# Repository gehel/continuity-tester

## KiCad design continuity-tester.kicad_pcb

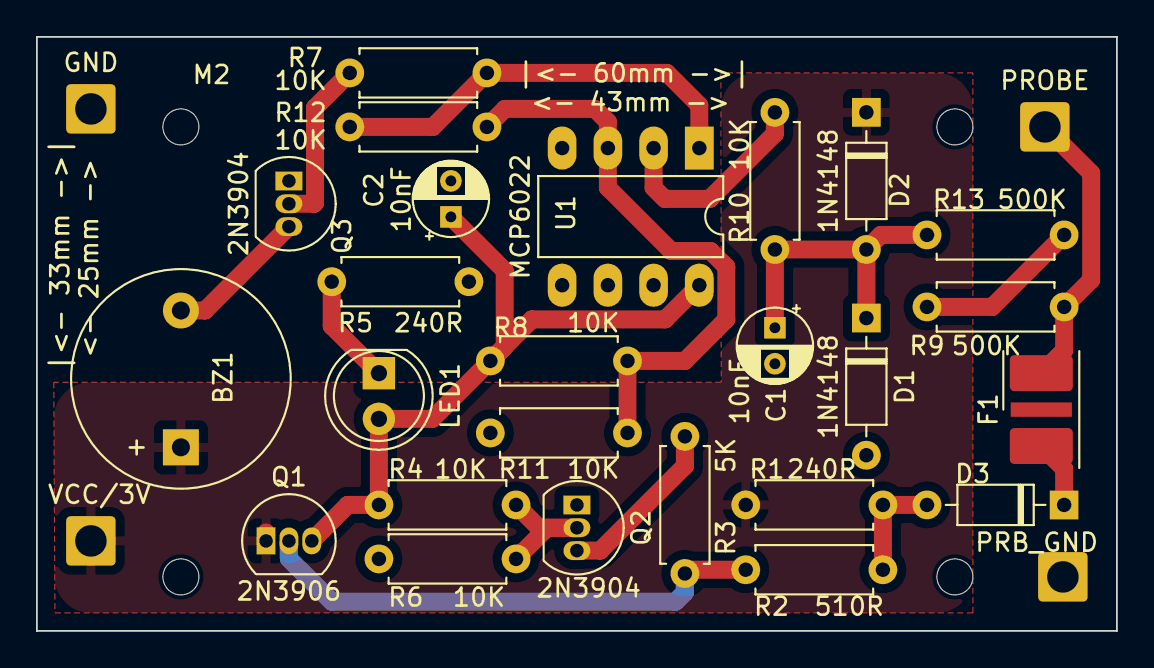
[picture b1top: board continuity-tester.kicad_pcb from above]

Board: 2 copper layers, 60.0 x 33.0 mm, 33 parts (0 on the bottom side), 17 nets.

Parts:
BZ1: Buzzer; Buzzer_12x9.5RM7.6
C1, C2: 10nF; CP_Radial_D4.0mm_P2.00mm
D1, D2: 1N4148; D_DO-35_SOD27_P7.62mm_Horizontal
D3: D; D_DO-35_SOD27_P7.62mm_Horizontal
F1: Polyfuse; Fuse_Bourns_TBU-CA
GND: Conn_01x01_Pin; SolderWire-1sqmm_1x01_D1.4mm_OD2.7mm
H1, H2, H3, H4: MountingHole_Pad; MountingHole_2mm
LED1: LED; LED_D5.0mm
PRB_GND: Conn_01x01_Pin; SolderWire-1sqmm_1x01_D1.4mm_OD2.7mm
PROBE: Conn_01x01_Pin; SolderWire-1sqmm_1x01_D1.4mm_OD2.7mm
Q1: 2N3906; TO-92_Inline
Q2, Q3: 2N3904; TO-92_Inline
R1, R5: 240R; R_Axial_DIN0207_L6.3mm_D2.5mm_P7.62mm_Horizontal
R2: 510R; R_Axial_DIN0207_L6.3mm_D2.5mm_P7.62mm_Horizontal
R3: 5K; R_Axial_DIN0207_L6.3mm_D2.5mm_P7.62mm_Horizontal
R4, R6, R7, R8, R10, R11, R12: 10K; R_Axial_DIN0207_L6.3mm_D2.5mm_P7.62mm_Horizontal
R9, R13: 500K; R_Axial_DIN0207_L6.3mm_D2.5mm_P7.62mm_Horizontal
U1: MCP6022; DIP-8_W7.62mm_LongPads
VCC/3V: Conn_01x01_Pin; SolderWire-1sqmm_1x01_D1.4mm_OD2.7mm

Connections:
GND: C1.2, C2.2, D1.2 (A), GND.1, PRB_GND.1, Q2.1 (E), Q3.1 (E), R5.1, R6.1, R11.1, U1.4 (V-)
unnamed: BZ1.2 (+), Q3.3 (C)
unnamed: C1.1, D1.1 (K), D2.2 (A), R10.1, R13.2
unnamed: D3.2 (A), R1.1, R2.1
unnamed: D3.1 (K), F1.1
unnamed: F1.2, PROBE.1, R9.1
unnamed: LED1.1 (K), R5.2
unnamed: Q1.2 (B), R2.2, R3.2
unnamed: Q2.2 (B), R4.1, R6.2
unnamed: Q2.3 (C), R3.1
unnamed: Q3.2 (B), R7.2
unnamed: R7.1, R12.2, U1.1
unnamed: R9.2, R13.1
unnamed: R8.1, R11.2, R12.1, U1.3 (+)
unnamed: R10.2, U1.2 (-)
POWER_SWITCHED: C2.1, LED1.2 (A), Q1.3 (C), R4.2, R8.2, U1.8 (V+)
VCC: BZ1.1 (-), D2.1 (K), Q1.1 (E), R1.2, VCC/3V.1

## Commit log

2023-06-28 added board dimensions to silkscreen
2023-07-31 Silkscreen
2023-07-31 Nicer planes
